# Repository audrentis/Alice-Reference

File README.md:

# Alice-Reference
* A kicad template project configurated for the Alice layout by Yuktsi 
 
* An FR4 plate using my footprints found [here](https://github.com/audrentis/MX_Plate_Footprints.pretty)

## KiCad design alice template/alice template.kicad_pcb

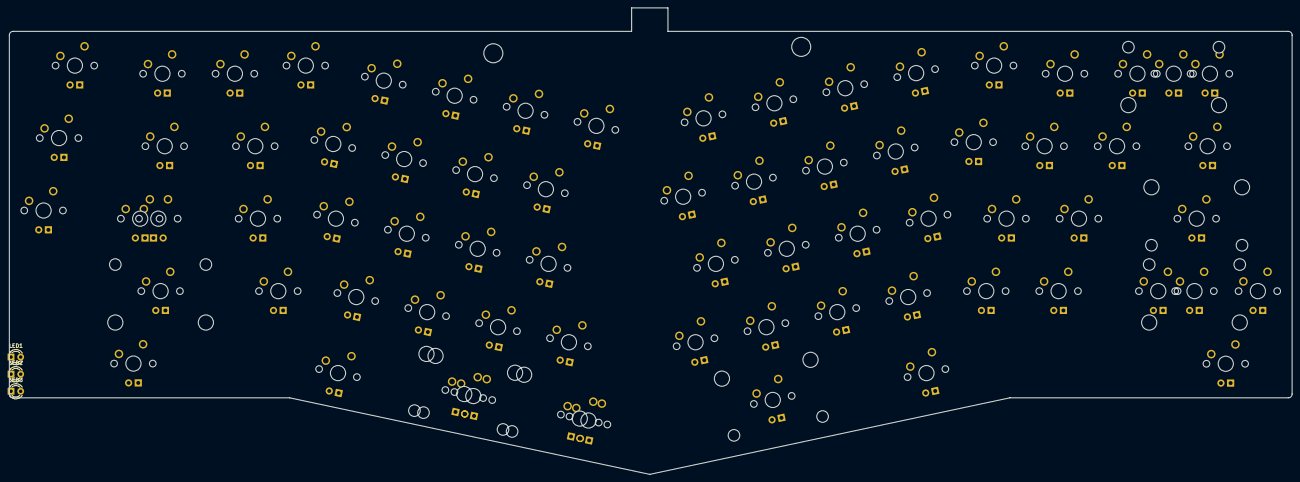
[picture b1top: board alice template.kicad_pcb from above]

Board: 2 copper layers, 337.2 x 122.6 mm, 147 parts (0 on the bottom side), 16 nets, no tracks yet.

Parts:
B1, B2, B3, B4, B5, B6, B6A1, B7, B8, B9, B10, B11, B12, B13, B14, B15, B16, B17, B18, B19, B20, B21, B22, B23, B24, B25, B26, B26A1, B27, B28, B29, B30, B31, B31A1, B32, B33, B34, B35, B36, B37, B38, B39, B40, B41, B42, B43, B44, B45, B46, B47, B48, B49, B50, B51, B52, B53, B54, B55, B56, B57, B58, B59, B59A1, B59A2, B60, B61, B62, B62A1, B62A2, B63, B64: LED; MXOnly-LEDONLY
H1, H2: MountingHole; MountingHole_5mm
LED1, LED2, LED3: LED; LED_D3.0mm
MX1, MX2, MX3, MX4, MX9, MX10, MX11, MX12, MX13, MX14, MX15, MX16, MX18, MX19, MX20, MX21, MX22, MX23, MX24, MX25, MX27, MX28, MX29, MX30, MX31, MX32, MX33, MX34, MX35, MX36, MX37, MX38, MX39, MX40, MX42, MX43, MX44, MX45, MX46, MX47, MX48, MX49, MX51, MX52, MX53, MX54, MX55, MX56, MX57, MX58, MX59A1, MX59A2, MX60, MX62A2: MX-NoLED; MXOnly-1U-NoLED
MX5, MX8, MX17, MX50, MX63, MX64: MX-NoLED; MXOnly-1.5U-NoLED
MX6, MX62A1: MX-NoLED; MXOnly-1.75U-NoLED
MX6A1, MX31A1: MX-NoLED; MXOnly-1.25U-NoLED
MX7: MX-NoLED; MXOnly-2.25U-NoLED
MX26, MX61: MX-NoLED; MXOnly-2.25U-ReversedStabilizers-NoLED
MX26A1: MX-NoLED; MXOnly-2U-ReversedStabilizers-NoLED
MX41: MX-NoLED; MXOnly-2.75U-ReversedStabilizers-NoLED
MX59: MX-NoLED; MXOnly-2U-NoLED
MX62: MX-NoLED; MXOnly-2.75U-NoLED

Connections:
unnamed: B6.1, B6A1.1
unnamed: B6.2, B6A1.2
unnamed: B26.1, B26A1.1
unnamed: B26.2, B26A1.2
unnamed: B31.1, B31A1.1
unnamed: B31.2, B31A1.2
unnamed: MX6.1, MX6A1.2
unnamed: MX6.2, MX6A1.1
unnamed: MX26.1, MX26A1.1
unnamed: MX26.2, MX26A1.2
unnamed: MX31.1, MX31A1.1
unnamed: MX31.2, MX31A1.2
unnamed: MX59.1, MX59A1.1
unnamed: MX59.2, MX59A1.2
unnamed: MX62.1, MX62A1.1
unnamed: MX62.2, MX62A1.2

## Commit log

2020-12-18 Add files
2020-12-18 Add Gerbers for plate
2021-01-12 make plate changes
